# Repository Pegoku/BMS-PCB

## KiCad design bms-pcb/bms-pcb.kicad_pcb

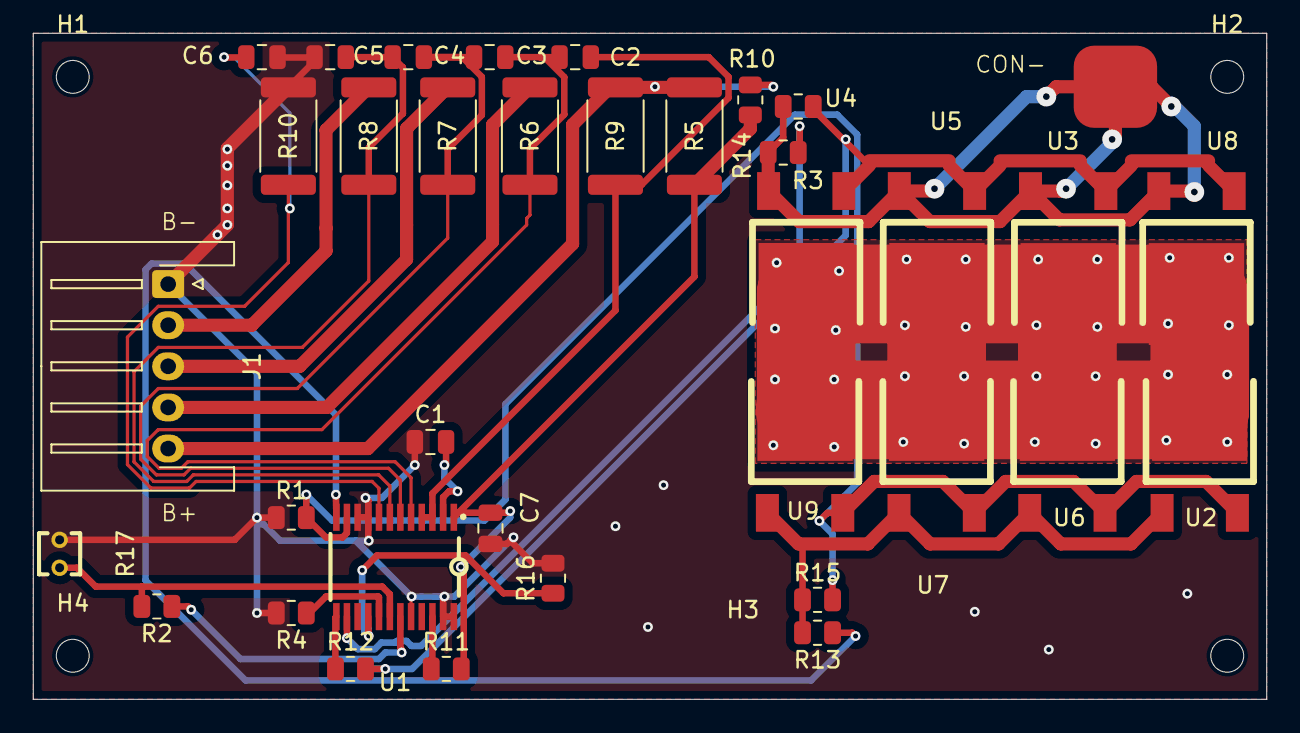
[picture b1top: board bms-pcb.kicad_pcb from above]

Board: 2 copper layers, 75.0 x 40.5 mm, 40 parts (0 on the bottom side), 25 nets.

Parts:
C1, C7: 1uF; C_0805_2012Metric
C2, C3, C4, C5, C6: 0.1uF; C_0805_2012Metric
H1, H2, H3, H4: MountingHole; MountingHole_2mm
J1: Conn_01x05; JST_XH_S5B-XH-A-1_1x05_P2.50mm_Horizontal
R1: R; R_0805_2012Metric
R2, R11, R16: 10k; R_0805_2012Metric
R3: 470k; R_0805_2012Metric
R4: 100k; R_0805_2012Metric
R5, R6, R7, R8, R9, R10#2: 1k; R_2512_6332Metric
R10, R12: 1k; R_0805_2012Metric
R13: 4.5k; R_0805_2012Metric
R14, R15: 1M; R_0805_2012Metric
R17: MF52A1103F3950(P334-4); RES-TH_L2.5-W2.5-P1.70-D0.3
TP2: TestPoint
U1: BQ7791500PWR; TSSOP-24_L7.8-W4.4-P0.65-LS6.4-BL
U2, U3, U4, U5, U6, U7, U8, U9: IRFR3707ZTRPBF-VB; TO-252-3_L6.5-W6.1-P4.58-LS9.9-BR

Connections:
D: U2.2 (D), U3.2 (D), U4.2 (D), U5.2 (D), U6.2 (D), U7.2 (D), U8.2 (D), U9.2 (D)
GND: C1.1, C5.1, C6.2, C7.1, J1.1, R1.1, R4.2, R10#2.1, R16.2, R17.1, U1.9 (VSS), U1.10 (SRP), U1.20 (CCFG), U1.23 (CTRC), U1.24 (CTRD)
unnamed: J1.2, R8.1
unnamed: J1.3, R7.1
unnamed: J1.4, R6.1
unnamed: C1.2, U1.2 (AVDD)
unnamed: R16.1, U1.16 (CBI)
unnamed: R12.1, U1.13 (CHG)
unnamed: R13.1, U1.12 (DSG)
unnamed: R3.1, U1.14 (LD)
unnamed: R4.1, U1.17 (OCDP)
unnamed: R11.1, U1.22 (PRES)
unnamed: R1.2, R15.2, U1.11 (SRN), U2.3 (S), U6.3 (S), U7.3 (S), U9.3 (S)
unnamed: R2.2, R17.2, U1.18 (TS)
unnamed: C6.1, R10#2.2, U1.8 (VC0)
unnamed: C4.1, C5.2, R8.2, U1.7 (VC1)
unnamed: C3.1, C4.2, R7.2, U1.6 (VC2)
unnamed: C2.1, C3.2, R6.2, U1.5 (VC3)
unnamed: C2.2, R9.2, U1.3 (VC5), U1.4 (VC4)
unnamed: C7.2, R5.2, R10.2, R11.2, U1.1 (VDD)
unnamed: R2.1, U1.19 (VTB)
unnamed: R13.2, R15.1, U2.1 (G), U6.1 (G), U7.1 (G), U9.1 (G)
unnamed: R12.2, R14.1, U3.1 (G), U4.1 (G), U5.1 (G), U8.1 (G)
Pack+: J1.5, R5.1, R9.1, R10.1
Pack-: R3.2, R14.2, TP2.1, U3.3 (S), U4.3 (S), U5.3 (S), U8.3 (S)

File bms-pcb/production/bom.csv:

Designator,Footprint,Quantity,Value,LCSC Part #
"C1, C7",0805,2,1uF,
"C2, C3, C4, C5, C6",0805,5,0.1uF,
J1,JST_XH_S5B-XH-A-1_1x05_P2.50mm_Horizontal,1,Conn_01x05,C2908614
R1,0805,1,R,
"R10_2, R12",0805,2,1k,
"R10, R5, R6, R7, R8, R9",2512,6,1k,
"R11, R16, R2",0805,3,10k,
R13,0805,1,4.5k,
"R14, R15",0805,2,1M,
R17,RES-TH_L2.5-W2.5-P1.70-D0.3,1,MF52A1103F3950(P334-4),C13879
R3,0805,1,470k,
R4,0805,1,100k,
TP2,TestPoint,1,TestPoint,
U1,TSSOP-24_L7.8-W4.4-P0.65-LS6.4-BL,1,BQ7791500PWR,C2876946
"U2, U3, U4, U5, U6, U7, U8, U9",TO-252-3_L6.5-W6.1-P4.58-LS9.9-BR,8,IRFR3707ZTRPBF-VB,C7463619

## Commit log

2024-10-15 finish
